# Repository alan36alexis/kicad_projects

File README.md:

# kicad_projects
This repository contains some personal projects made in Kicad

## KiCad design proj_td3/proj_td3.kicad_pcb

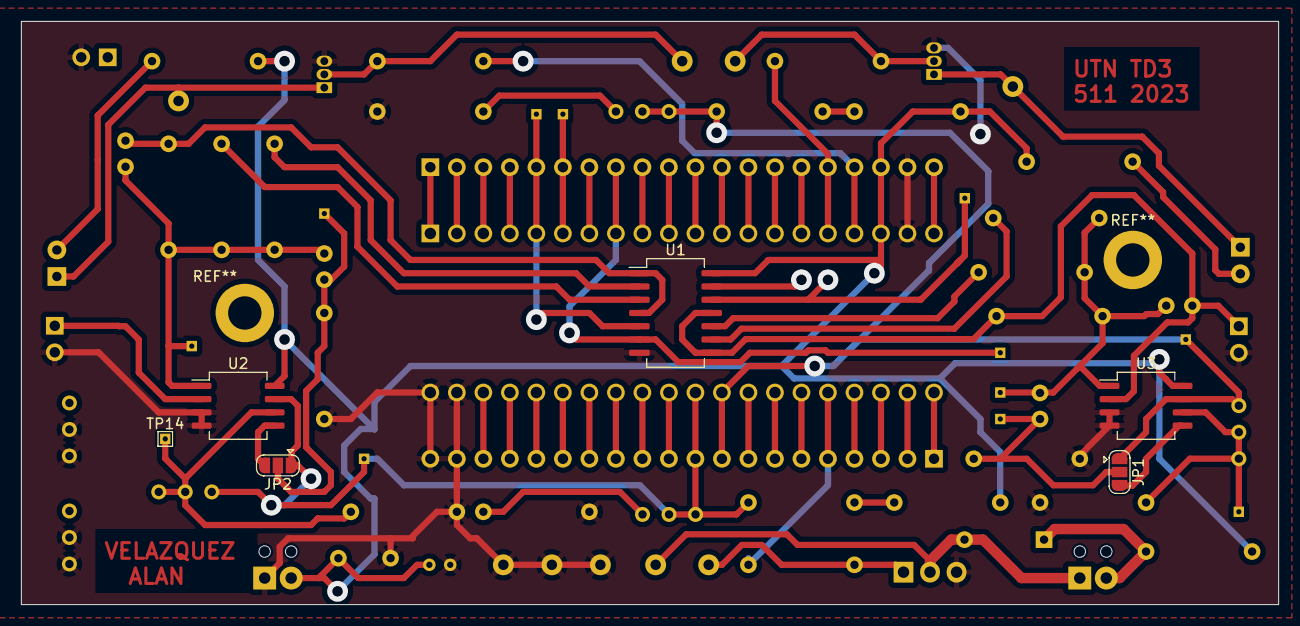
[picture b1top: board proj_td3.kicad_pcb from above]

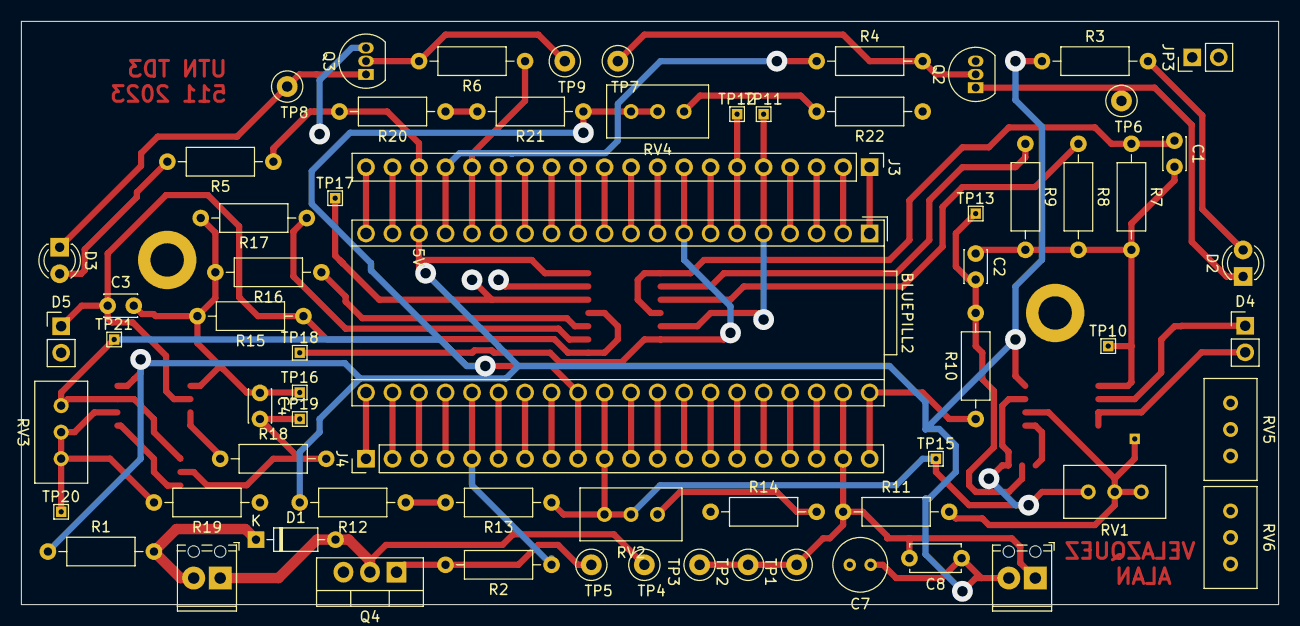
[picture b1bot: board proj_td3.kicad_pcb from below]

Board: 2 copper layers, 120.5 x 55.9 mm, 74 parts (68 on the bottom side), 64 nets.

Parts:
BLUEPILL2: Electrosmith_Daisy_Seed
C1, C3: 12p; C_Disc_D3.0mm_W2.0mm_P2.50mm
C2, C4: 100n; C_Disc_D3.0mm_W2.0mm_P2.50mm
C7: C_Polarized; C_Radial_D5.0mm_H5.0mm_P2.00mm
C8: 2.2n; C_Disc_D4.7mm_W2.5mm_P5.00mm
D1: 1N4148; D_DO-35_SOD27_P7.62mm_Horizontal
D2, D3: TX LED (white); LED_D3.0mm
D4, D5: D_Photo; PinHeader_1x02_P2.54mm_Vertical
J1: Motor; TerminalBlock_Phoenix_MPT-0,5-2-2.54_1x02_P2.54mm_Horizontal
J2: Input 5V; TerminalBlock_Phoenix_MPT-0,5-2-2.54_1x02_P2.54mm_Horizontal
J3, J4: Conn_01x20_Socket; PinHeader_1x20_P2.54mm_Vertical
JP1, JP2: SolderJumper_3_Open; SolderJumper-3_P1.3mm_Open_RoundedPad1.0x1.5mm
JP3: Jumper_2_Open; PinHeader_1x02_P2.54mm_Vertical
Q2, Q3: BC546; TO-92_Inline
Q4: TIP122; TO-220-3_Vertical
R1: DNP; R_Axial_DIN0207_L6.3mm_D2.5mm_P10.16mm_Horizontal
R2, R4, R6, R11, R19: 1k; R_Axial_DIN0207_L6.3mm_D2.5mm_P10.16mm_Horizontal
R3, R5: 270; R_Axial_DIN0207_L6.3mm_D2.5mm_P10.16mm_Horizontal
R7, R8, R15, R16: 1M; R_Axial_DIN0207_L6.3mm_D2.5mm_P10.16mm_Horizontal
R9, R17: 470k; R_Axial_DIN0207_L6.3mm_D2.5mm_P10.16mm_Horizontal
R10, R13, R18, R21: 10k; R_Axial_DIN0207_L6.3mm_D2.5mm_P10.16mm_Horizontal
R12, R20: 47k; R_Axial_DIN0207_L6.3mm_D2.5mm_P10.16mm_Horizontal
R14, R22: 100k; R_Axial_DIN0207_L6.3mm_D2.5mm_P10.16mm_Horizontal
RV1, RV3, RV5, RV6: 10k; Potentiometer_Bourns_3296W_Vertical
RV2, RV4: 50k; Potentiometer_Bourns_3296W_Vertical
TP1, TP2, TP3, TP4, TP5, TP6, TP7, TP8, TP9: TestPoint; TestPoint_Loop_D1.80mm_Drill1.0mm_Beaded
TP10, TP11, TP12, TP13, TP14, TP15, TP16, TP17, TP18, TP19, TP20, TP21: TestPoint; TestPoint_THTPad_1.0x1.0mm_Drill0.5mm
U1: 4066; SO-14_5.3x10.2mm_P1.27mm
U2, U3: LM358; SO-8_5.3x6.2mm_P1.27mm

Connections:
+3.3V: BLUEPILL2.20 (3V3), BLUEPILL2.38 (3V3), J3.20, J4.18
+5V: BLUEPILL2.18 (5V), C7.1, C8.1, J2.2, J3.18, R1.1, R3.1, R5.1, R12.2, R20.2, U1.14 (VDD), U2.8 (V+), U3.8 (V+)
ADC4 (Muestreo FSK 2): BLUEPILL2.29 (PA4), J4.9, JP1.1 (A), R21.1, RV3.1, RV4.1, RV4.2, TP21.1, U3.7
ADC5 (Muestreo FSK 1): BLUEPILL2.30 (PA5), J4.10, JP2.1 (A), R13.1, RV1.1, RV2.1, RV2.2, TP15.1, U2.7
ADC8 (Seteo distancia): BLUEPILL2.33 (PB0), J4.13, RV6.3
ADC9 (Seteo velocidad): BLUEPILL2.34 (PB1), J4.14, RV5.3
EXT IT (Input modo): BLUEPILL2.1 (PB12), J3.1, JP3.1 (A)
GCA1: BLUEPILL2.5 (PA8), J3.5, TP11.1, U1.5
GCA2: BLUEPILL2.6 (PA9), J3.6, TP12.1, U1.13
GCB1: BLUEPILL2.7 (PA10), J3.7, TP17.1, U1.12
GCB2: BLUEPILL2.8 (PA11), J3.8, TP18.1, U1.6
GND: BLUEPILL2.19 (GND), BLUEPILL2.39 (GND), BLUEPILL2.40 (GND), C7.2, C8.2, D4.2 (A), D5.2 (A), J2.1, J3.19, J4.19, J4.20, JP3.2 (B), Q2.3 (E), Q3.3 (E), Q4.3 (E), R10.1, R11.1, R14.1, R18.1, R19.1, R22.1, RV5.1, RV5.2, RV6.1, RV6.2, TP1.1, TP2.1, TP3.1, U1.7 (VSS), U2.3 (+), U2.4 (V-), U3.3 (+), U3.4 (V-)
Motor control: BLUEPILL2.31 (PA6), J4.11
NRST: BLUEPILL2.37 (NRST), J4.17
unnamed: C1.2, C2.1, R7.2, R8.2, R9.2, TP10.1, U2.1
unnamed: C3.2, C4.1, R15.2, R16.2, R17.2, TP16.1, U3.1
unnamed: D1.2 (A), J1.1, Q4.2 (C), TP4.1
unnamed: D1.1 (K), J1.2, R1.2
unnamed: D2.2 (A), R3.2
unnamed: D2.1 (K), Q2.1 (C), TP6.1
unnamed: D3.2 (A), R5.2
unnamed: D3.1 (K), Q3.1 (C), TP8.1
unnamed: C1.1, D4.1 (K), R7.1, U1.1, U1.4, U2.2 (-)
unnamed: C3.1, D5.1 (K), R15.1, U1.8, U1.11, U3.2 (-)
unnamed: JP1.3 (B), U3.5 (+)
unnamed: C4.2, JP1.2 (C), R18.2, TP19.1
unnamed: JP2.3 (B), U2.5 (+)
unnamed: C2.2, JP2.2 (C), R10.2, TP13.1
unnamed: Q2.2 (B), R4.2, TP7.1
unnamed: Q3.2 (B), R6.2, TP9.1
unnamed: Q4.1 (B), R2.2, TP5.1
unnamed: R8.1, U1.3
unnamed: R9.1, U1.2
unnamed: R12.1, R13.2
unnamed: R14.2, RV2.3
unnamed: R16.1, U1.10
unnamed: R17.1, U1.9
unnamed: R20.1, R21.2
unnamed: R22.2, RV4.3
unnamed: R11.2, RV1.2, RV1.3, TP14.1, U2.6 (-)
unnamed: R19.2, RV3.2, RV3.3, TP20.1, U3.6 (-)
PA1: BLUEPILL2.26 (PA1), J4.6
PA7: BLUEPILL2.32 (PA7), J4.12
PA12: BLUEPILL2.9 (PA12), J3.9
PA15: BLUEPILL2.10 (PA15), J3.10
PB3: BLUEPILL2.11 (PB3), J3.11
PB4: BLUEPILL2.12 (PB4), J3.12
PB5: BLUEPILL2.13 (PB5), J3.13
PB6: BLUEPILL2.14 (PB6), J3.14
PB7: BLUEPILL2.15 (PB7), J3.15
PB13: BLUEPILL2.2 (PB13), J3.2
PB14: BLUEPILL2.3 (PB14), J3.3
PB15: BLUEPILL2.4 (PB15), J3.4
PC13: BLUEPILL2.22 (PC13), J4.2
PC14: BLUEPILL2.23 (PC14), J4.3
PC15: BLUEPILL2.24 (PC15), J4.4
SCL2 (Display): BLUEPILL2.35 (PB10), J4.15
SDA2 (Display): BLUEPILL2.36 (PB11), J4.16
T2C1 (PWM Motor): BLUEPILL2.25 (PA0), J4.5, R2.1
T4C3 (Señal LED FSK 2): BLUEPILL2.16 (PB8), J3.16, R6.1
T4C4 (Señal LED FSK 1): BLUEPILL2.17 (PB9), J3.17, R4.1
USART2-RX: BLUEPILL2.28 (PA3), J4.8
USART2-TX: BLUEPILL2.27 (PA2), J4.7
VBAT: BLUEPILL2.21 (VBAT), J4.1

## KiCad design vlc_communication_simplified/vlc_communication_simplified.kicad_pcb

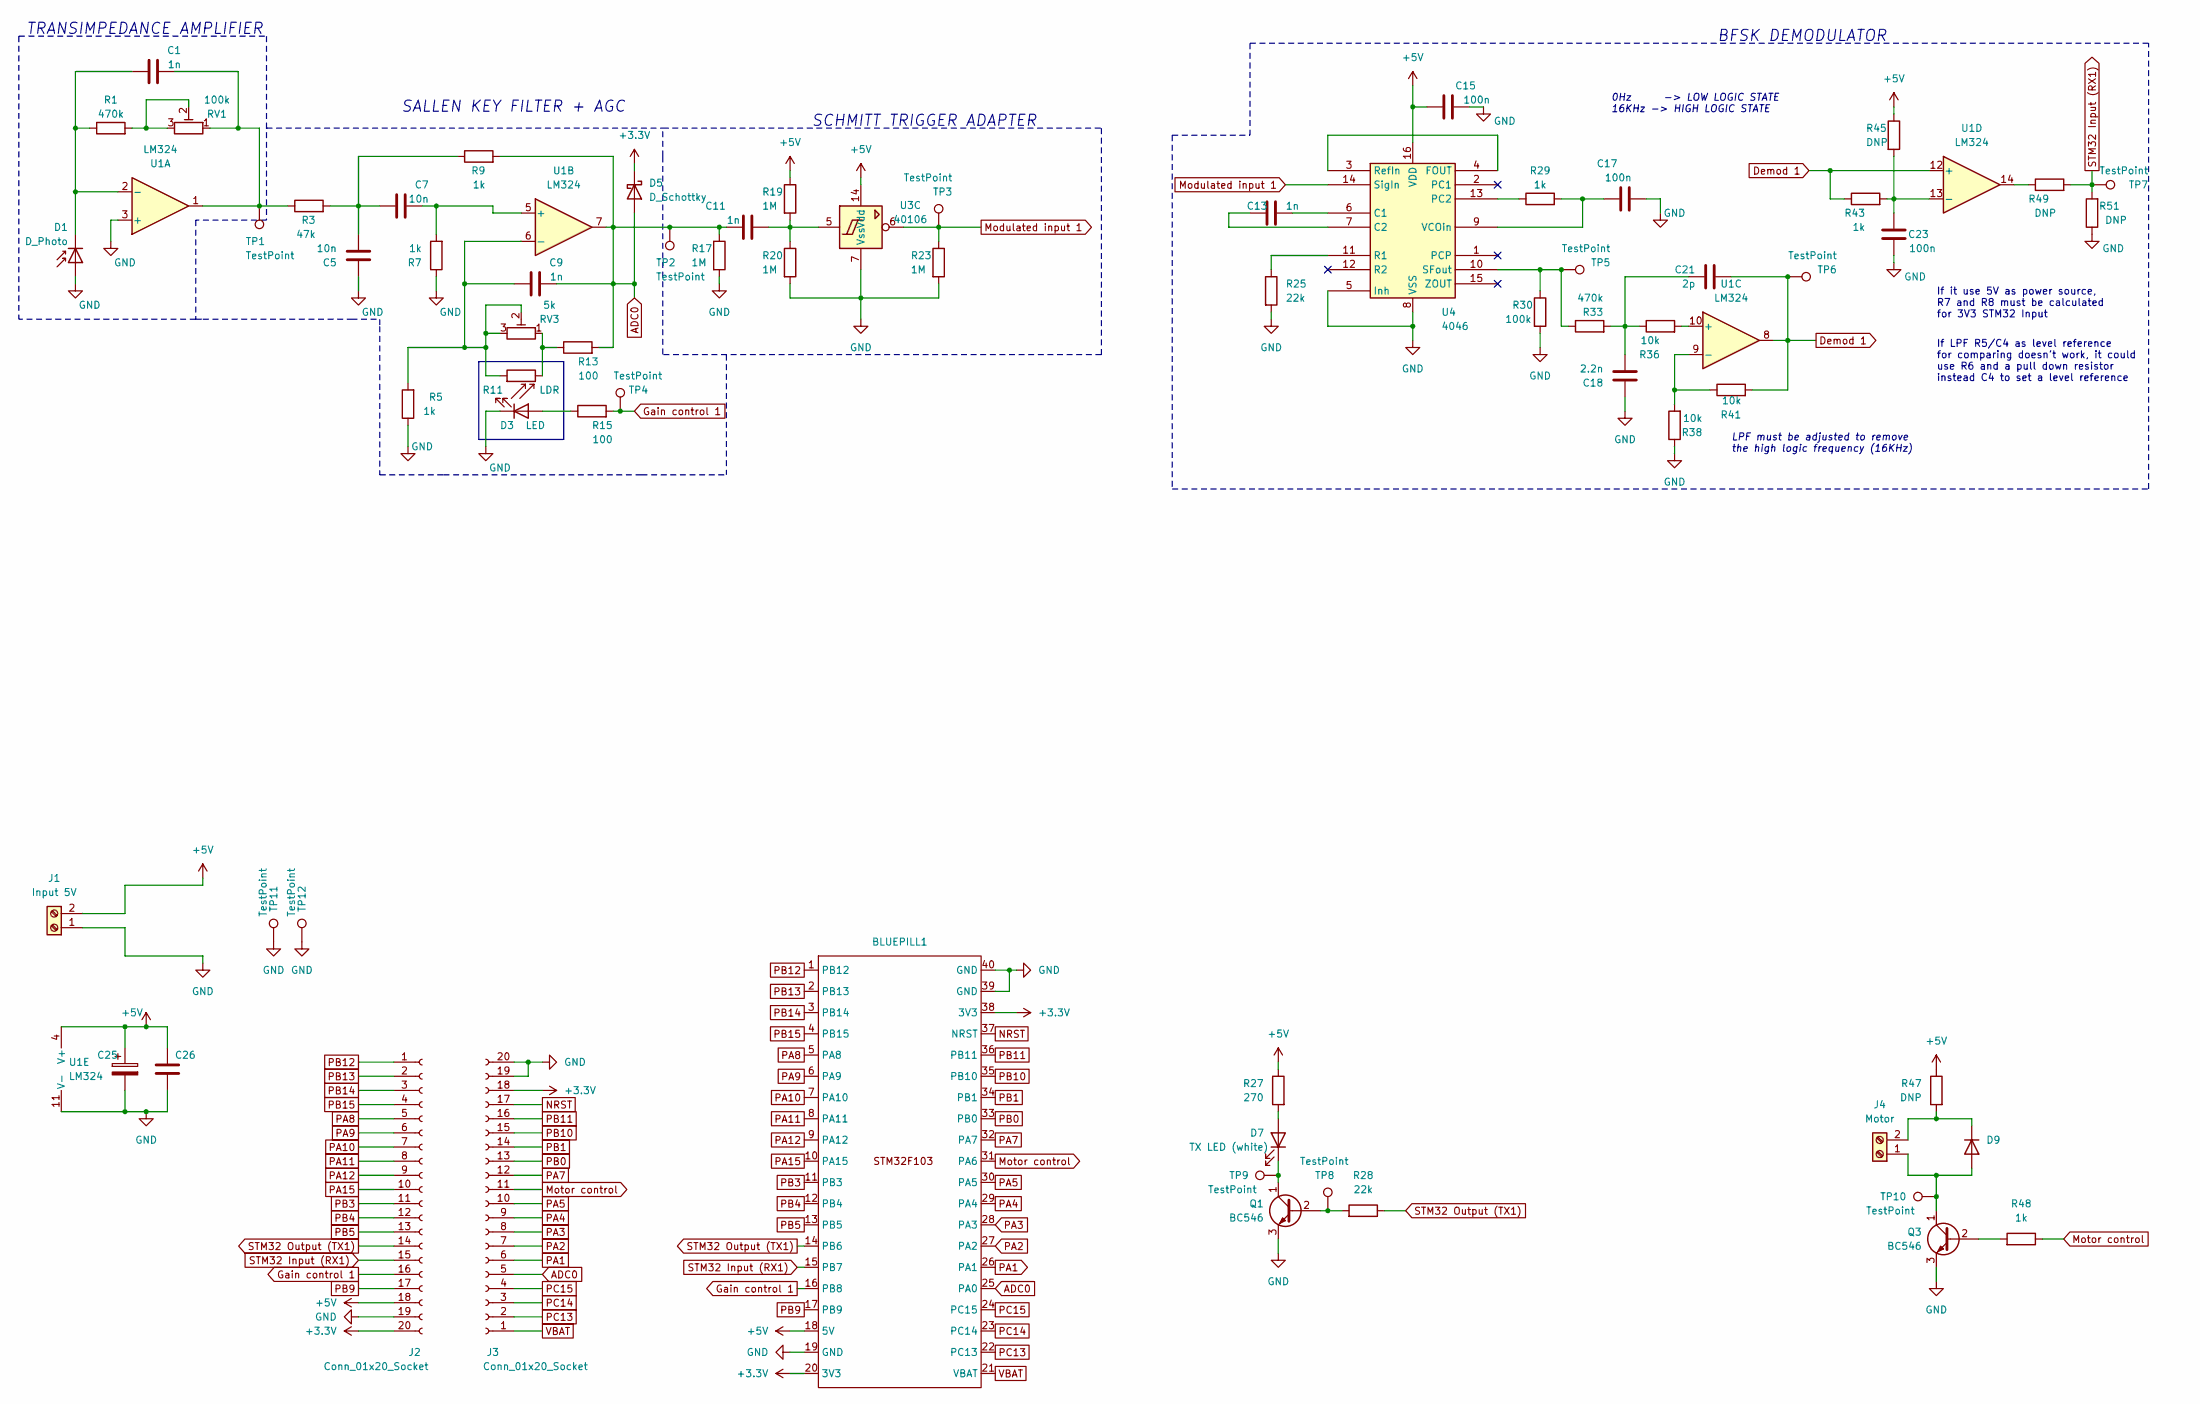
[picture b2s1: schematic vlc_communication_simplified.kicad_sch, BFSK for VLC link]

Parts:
BLUEPILL1: Electrosmith_Daisy_Seed
C1, C9, C11, C13: 1n; C_Disc_D4.7mm_W2.5mm_P5.00mm
C5, C7: 10n; C_Disc_D4.7mm_W2.5mm_P5.00mm
C15, C17, C23: 100n; C_Disc_D4.7mm_W2.5mm_P5.00mm
C18, C26: 2.2n; C_Disc_D4.7mm_W2.5mm_P5.00mm
C21: 2p; C_Disc_D4.7mm_W2.5mm_P5.00mm
C25: C_Polarized; C_Radial_D5.0mm_H5.0mm_P2.00mm
D1: D_Photo; PinHeader_1x02_P2.54mm_Vertical
D3: LED; LED_D3.0mm
D5: D_Schottky; D_DO-35_SOD27_P7.62mm_Horizontal
D7: TX LED (white); LED_D3.0mm
D9: 1N4148; D_DO-35_SOD27_P7.62mm_Horizontal
J1: Input 5V; TerminalBlock_Phoenix_MKDS-1,5-2-5.08_1x02_P5.08mm_Horizont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
J2, J3: Conn_01x20_Socket; PinHeader_1x20_P2.54mm_Vertical
J4: Motor; TerminalBlock_Phoenix_MKDS-1,5-2-5.08_1x02_P5.08mm_Horizont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
Q1, Q3: BC546; TO-92_Inline
R1, R33: 470k; R_Axial_DIN0207_L6.3mm_D2.5mm_P10.16mm_Horizontal
R3: 47k; R_Axial_DIN0207_L6.3mm_D2.5mm_P10.16mm_Horizontal
R5, R7, R9, R29, R43, R48: 1k; R_Axial_DIN0207_L6.3mm_D2.5mm_P10.16mm_Horizontal
R11: LDR; PinHeader_1x02_P2.54mm_Vertical
R13, R15: 100; R_Axial_DIN0207_L6.3mm_D2.5mm_P10.16mm_Horizontal
R17, R19, R20, R23: 1M; R_Axial_DIN0207_L6.3mm_D2.5mm_P10.16mm_Horizontal
R25, R28: 22k; R_Axial_DIN0207_L6.3mm_D2.5mm_P10.16mm_Horizontal
R27: 270; R_Axial_DIN0207_L6.3mm_D2.5mm_P10.16mm_Horizontal
R30: 100k; R_Axial_DIN0207_L6.3mm_D2.5mm_P10.16mm_Horizontal
R36, R38, R41: 10k; R_Axial_DIN0207_L6.3mm_D2.5mm_P10.16mm_Horizontal
R45, R47, R49, R51: DNP; R_Axial_DIN0207_L6.3mm_D2.5mm_P10.16mm_Horizontal
RV1: 100k; Potentiometer_Bourns_3296W_Vertical
RV3: 5k; Potentiometer_Bourns_3296W_Vertical
TP1, TP2, TP3, TP4, TP5, TP6, TP7, TP8, TP9, TP10, TP11, TP12: TestPoint; TestPoint_Loop_D1.80mm_Drill1.0mm_Beaded
U1: LM324; DIP-14_W7.62mm_Socket_LongPads
U3: 40106; DIP-14_W7.62mm_Socket_LongPads
U4: 4046; DIP-16_W7.62mm_Socket_LongPads

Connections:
+3.3V: BLUEPILL1.20 (3V3), BLUEPILL1.38 (3V3), D5.1 (K), J2.20, J3.18
+5V: BLUEPILL1.18 (5V), C15.1, C25.1, C26.1, J1.2, J2.18, R19.1, R27.1, R45.1, R47.1, U1.4 (V+), U3.14 (Vdd), U4.16 (VDD)
ADC0: BLUEPILL1.25 (PA0), C9.2, C11.1, D5.2 (A), J3.5, R9.2, R13.2, R17.1, TP2.1, U1.7
Demod 1: C21.2, R41.2, R43.1, TP6.1, U1.8, U1.12 (+)
GND: BLUEPILL1.19 (GND), BLUEPILL1.39 (GND), BLUEPILL1.40 (GND), C5.1, C15.2, C17.2, C18.1, C23.1, C25.2, C26.2, D1.2 (A), D3.1 (K), J1.1, J2.19, J3.19, J3.20, Q1.3 (E), Q3.3 (E), R5.1, R7.1, R17.2, R20.2, R23.2, R25.2, R30.2, R38.1, R51.1, TP11.1, TP12.1, U1.3 (+), U1.11 (V-), U3.7 (Vss), U4.5 (Inh), U4.8 (VSS)
Gain control 1: BLUEPILL1.16 (PB8), J2.16, R15.2, TP4.1
Modulated input 1: R23.1, TP3.1, U3.6, U4.14 (SigIn)
Motor control: BLUEPILL1.31 (PA6), J3.11, R48.1
NRST: BLUEPILL1.37 (NRST), J3.17
unnamed: C1.2, R3.1, RV1.1, TP1.1, U1.1
unnamed: C5.2, C7.1, R3.2, R9.1
unnamed: C11.2, R19.2, R20.1, U3.5
unnamed: C18.2, C21.1, R33.2, R36.1
unnamed: C1.1, D1.1 (K), R1.1, U1.2 (-)
unnamed: D3.2 (A), R15.1
unnamed: D7.2 (A), R27.2
unnamed: D7.1 (K), Q1.1 (C), TP9.1
unnamed: D9.2 (A), J4.1, Q3.1 (C), TP10.1
unnamed: D9.1 (K), J4.2, R47.2
unnamed: Q1.2 (B), R28.2, TP8.1
unnamed: Q3.2 (B), R48.2
unnamed: R1.2, RV1.2, RV1.3
unnamed: R11.2, R13.1, RV3.1
unnamed: R49.1, U1.14
unnamed: C7.2, R7.2, U1.5 (+)
unnamed: C9.1, R5.2, R11.1, RV3.2, RV3.3, U1.6 (-)
unnamed: R36.2, U1.10 (+)
unnamed: R38.2, R41.1, U1.9 (-)
unnamed: C23.2, R43.2, R45.2, U1.13 (-)
unnamed: C13.2, U4.6 (C1)
unnamed: C13.1, U4.7 (C2)
unnamed: U4.3 (RefIn), U4.4 (FOUT)
unnamed: R29.1, U4.13 (PC2)
unnamed: R25.1, U4.11 (R1)
unnamed: R30.1, R33.1, TP5.1, U4.10 (SFout)
unnamed: C17.1, R29.2, U4.9 (VCOin)
PA1: BLUEPILL1.26 (PA1), J3.6
PA2: BLUEPILL1.27 (PA2), J3.7
PA3: BLUEPILL1.28 (PA3), J3.8
PA4: BLUEPILL1.29 (PA4), J3.9
PA5: BLUEPILL1.30 (PA5), J3.10
PA7: BLUEPILL1.32 (PA7), J3.12
PA8: BLUEPILL1.5 (PA8), J2.5
PA9: BLUEPILL1.6 (PA9), J2.6
PA10: BLUEPILL1.7 (PA10), J2.7
PA11: BLUEPILL1.8 (PA11), J2.8
PA12: BLUEPILL1.9 (PA12), J2.9
PA15: BLUEPILL1.10 (PA15), J2.10
PB0: BLUEPILL1.33 (PB0), J3.13
PB1: BLUEPILL1.34 (PB1), J3.14
PB3: BLUEPILL1.11 (PB3), J2.11
PB4: BLUEPILL1.12 (PB4), J2.12
PB5: BLUEPILL1.13 (PB5), J2.13
PB9: BLUEPILL1.17 (PB9), J2.17
PB10: BLUEPILL1.35 (PB10), J3.15
PB11: BLUEPILL1.36 (PB11), J3.16
PB12: BLUEPILL1.1 (PB12), J2.1
PB13: BLUEPILL1.2 (PB13), J2.2
PB14: BLUEPILL1.3 (PB14), J2.3
PB15: BLUEPILL1.4 (PB15), J2.4
PC13: BLUEPILL1.22 (PC13), J3.2
PC14: BLUEPILL1.23 (PC14), J3.3
PC15: BLUEPILL1.24 (PC15), J3.4
STM32 Input (RX1): BLUEPILL1.15 (PB7), J2.15, R49.2, R51.2, TP7.1
STM32 Output (TX1): BLUEPILL1.14 (PB6), J2.14, R28.1
VBAT: BLUEPILL1.21 (VBAT), J3.1

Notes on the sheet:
SALLEN KEY FILTER + AGC
LPF must be adjusted to remove the high logic frequency (16KHz)
TRANSIMPEDANCE AMPLIFIER
If LPF R5/C4 as level reference for comparing doesn't work, it could use R6 and a pull down resistor instead C4 to set a level reference
SCHMITT TRIGGER ADAPTER
0Hz -> LOW LOGIC STATE 16KHz -> HIGH LOGIC STATE
If it use 5V as power source, R7 and R8 must be calculated for 3V3 STM32 Input
BFSK DEMODULATOR

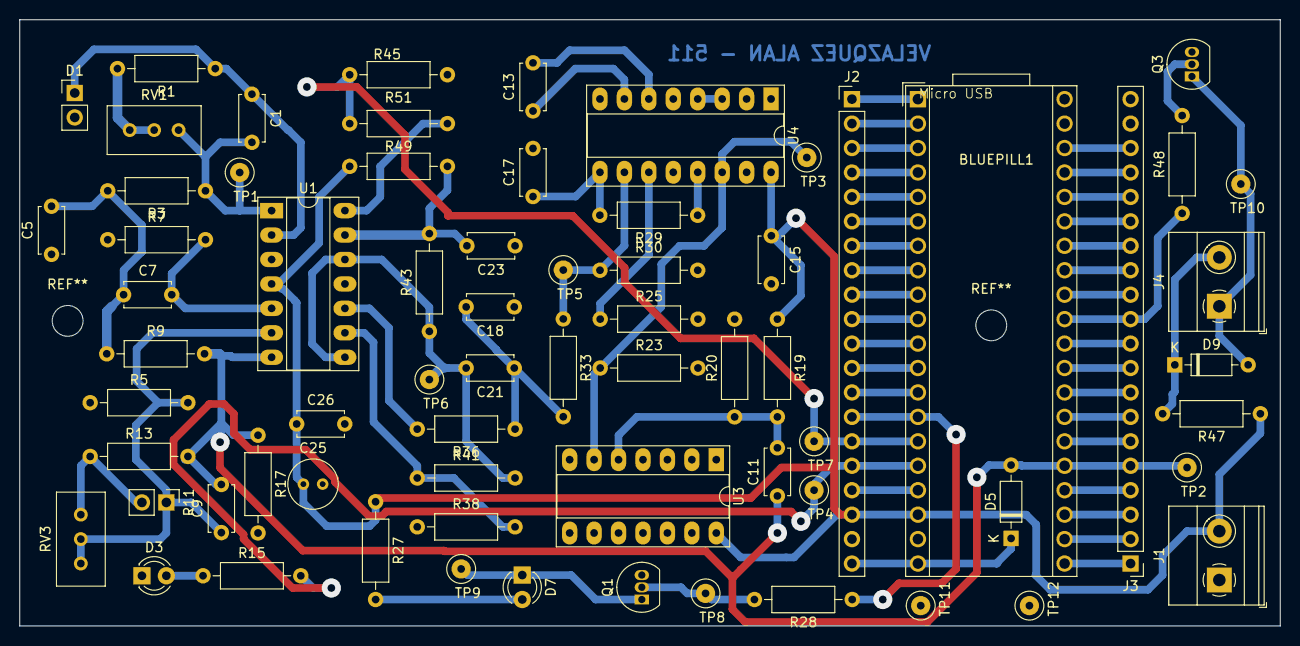
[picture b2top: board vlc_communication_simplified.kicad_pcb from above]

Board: 2 copper layers, 131.0 x 63.0 mm, 69 parts (0 on the bottom side), 66 nets.

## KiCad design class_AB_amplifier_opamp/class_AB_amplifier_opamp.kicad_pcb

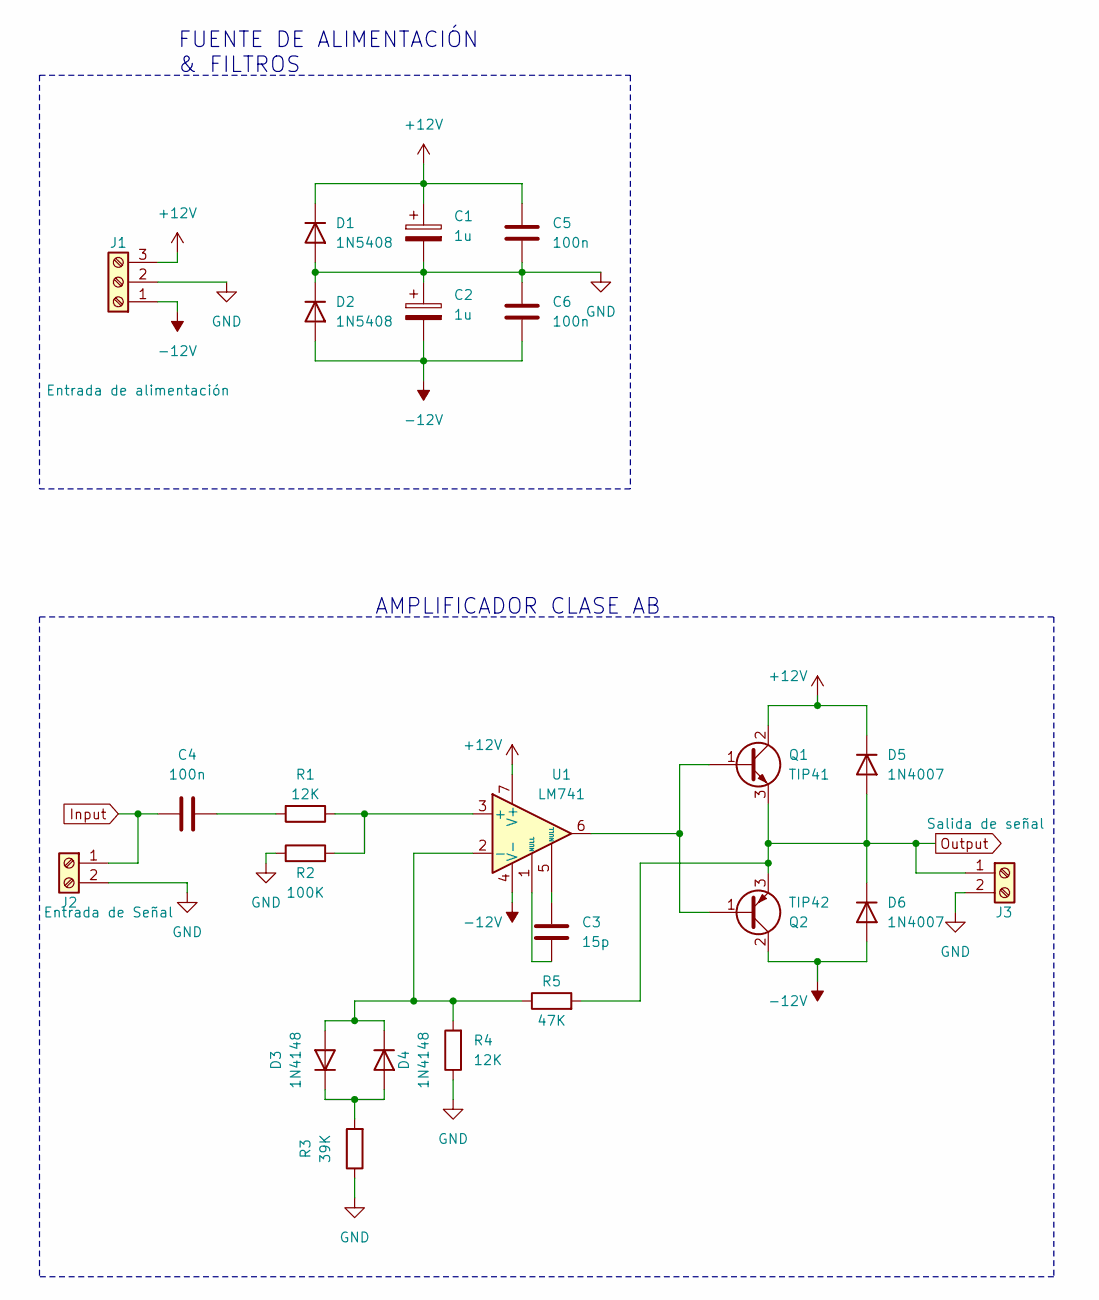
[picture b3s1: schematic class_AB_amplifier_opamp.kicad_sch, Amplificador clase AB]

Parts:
C1, C2: 1u; CP_Radial_D8.0mm_P5.00mm
C3: 15p; C_Disc_D4.7mm_W2.5mm_P5.00mm
C4, C5, C6: 100n; C_Disc_D4.7mm_W2.5mm_P5.00mm
D1, D2: 1N5408; D_DO-201AD_P15.24mm_Horizontal
D3, D4: 1N4148; D_DO-35_SOD27_P7.62mm_Horizontal
D5, D6: 1N4007; D_DO-41_SOD81_P10.16mm_Horizontal
J1: Entrada de alimentación; TerminalBlock_bornier-3_P5.08mm
J2: Entrada de Señal; TerminalBlock_bornier-2_P5.08mm
J3: Salida de señal; TerminalBlock_bornier-2_P5.08mm
Q1: TIP41; TO-220-3_Vertical
Q2: TIP42; TO-220-3_Vertical
R1, R4: 12K; R_Axial_DIN0207_L6.3mm_D2.5mm_P10.16mm_Horizontal
R2: 100K; R_Axial_DIN0207_L6.3mm_D2.5mm_P10.16mm_Horizontal
R3: 39K; R_Axial_DIN0207_L6.3mm_D2.5mm_P10.16mm_Horizontal
R5: 47K; R_Axial_DIN0207_L6.3mm_D2.5mm_P10.16mm_Horizontal
U1: LM741; DIP-8_W7.62mm_Socket

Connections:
+12V: C1.1, C5.2, D1.1 (K), D5.1 (K), J1.3, Q1.2 (C), U1.7 (V+)
-12V: C2.2, C6.1, D2.2 (A), D6.2 (A), J1.1, Q2.2 (C), U1.4 (V-)
GND: C1.2, C2.1, C5.1, C6.2, D1.2 (A), D2.1 (K), J1.2, J2.2, J3.2, R2.1, R3.1, R4.1
Input: C4.1, J2.1
unnamed: C3.1, U1.1 (NULL)
unnamed: C3.2, U1.5 (NULL)
unnamed: C4.2, R1.2
unnamed: D3.2 (A), D4.1 (K), R4.2, R5.1, U1.2 (-)
unnamed: D3.1 (K), D4.2 (A), R3.2
unnamed: Q1.1 (B), Q2.1 (B), U1.6
unnamed: R1.1, R2.2, U1.3 (+)
Output: D5.2 (A), D6.1 (K), J3.1, Q1.3 (E), Q2.3 (E), R5.2

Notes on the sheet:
AMPLIFICADOR CLASE AB
FUENTE DE ALIMENTACIÓN & FILTROS

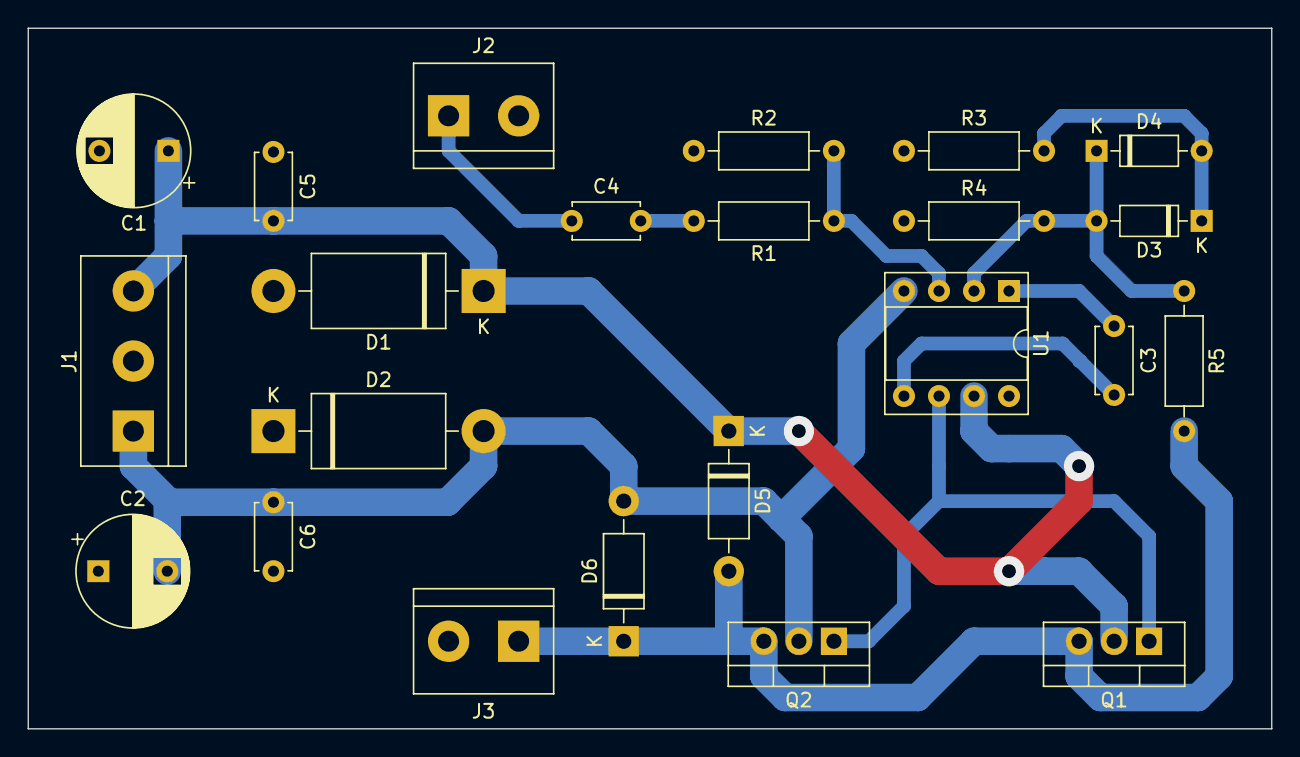
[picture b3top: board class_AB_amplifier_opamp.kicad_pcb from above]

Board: 2 copper layers, 90.2 x 50.8 mm, 23 parts (0 on the bottom side), 12 nets.

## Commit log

2023-09-16 bfsk version 2 frecuencias
2023-09-17 agrego bfsk ultima implementacion
2023-09-18 agrego tia usado actualmente
2023-09-25 agrego amplificador clase AB
2023-09-25 pdfs esquematico y pcb
2023-12-05 actualizo con proy td3
2023-12-11 avances de proyecto
2024-02-08 actualizo repo con proj-td3
2024-02-09 proj td3 avances
2024-02-10 avances proyecto td3
2024-02-17 avances proj td3
